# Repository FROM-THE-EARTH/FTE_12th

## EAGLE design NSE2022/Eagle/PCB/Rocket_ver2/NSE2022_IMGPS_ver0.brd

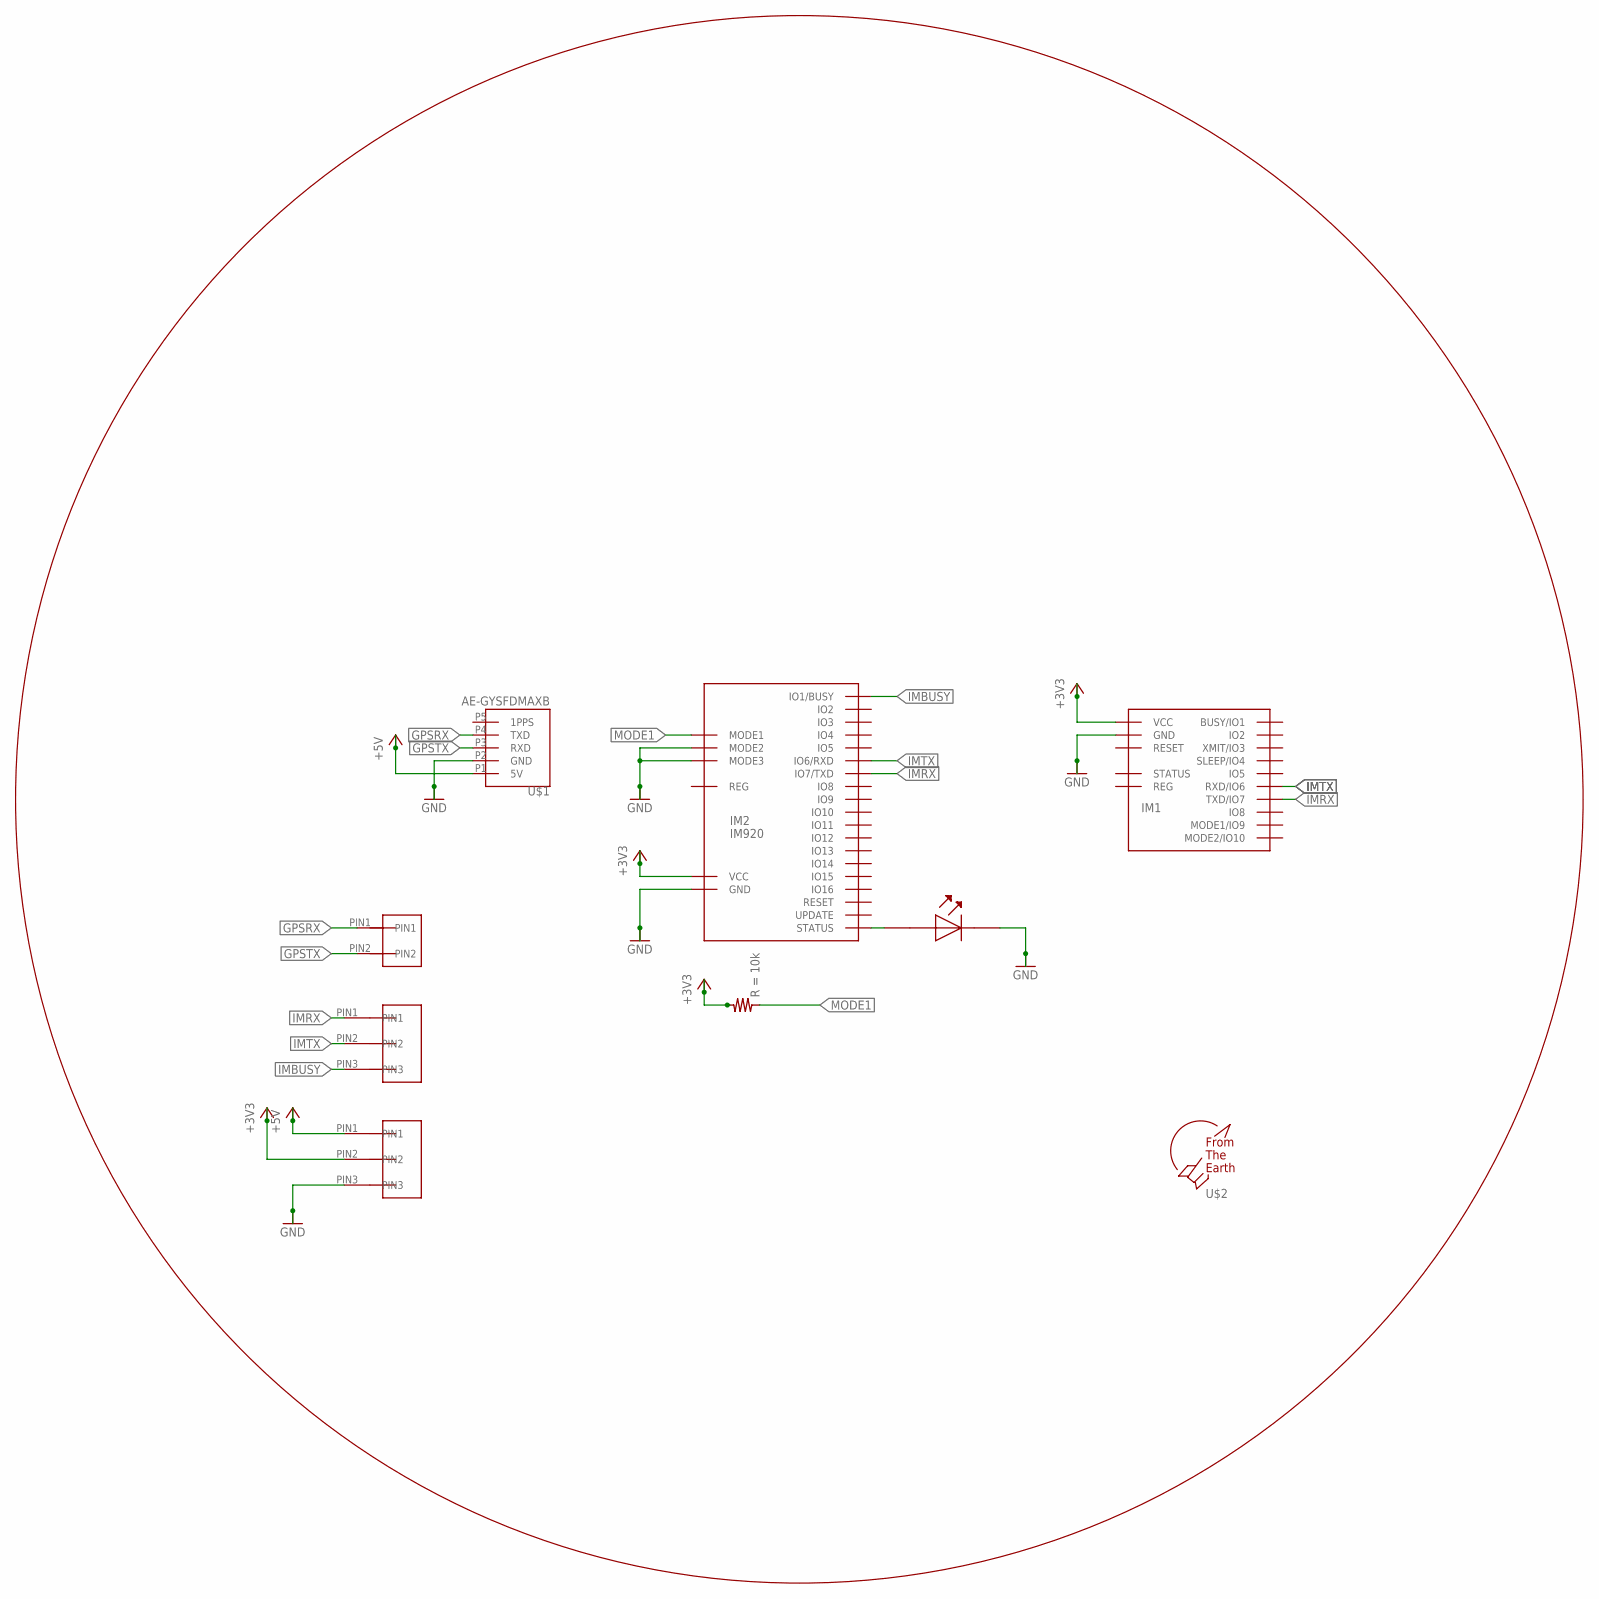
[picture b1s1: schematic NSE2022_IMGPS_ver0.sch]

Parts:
IM1: IM920C
IM2: IM920
R4: RESISTER; REGISTER
U$1: AE-GYSFDMAXB
U$2: F.T.E.LOGO; LOGO
U$33: 2PIN
U$47, U$48: 3PIN
U$54: LED

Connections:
+3V3: IM1.$P17 (VCC), IM2.IO23 (VCC), R4.B, U$48.PIN2
+5V: U$1.P1 (5V), U$48.PIN1
GND: IM1.$P18 (GND), IM2.IO18 (MODE2), IM2.IO19 (MODE3), IM2.IO24 (GND), U$1.P2 (GND), U$48.PIN3, U$54.PLUS (OUT)
GPSRX: U$1.P4 (TXD), U$33.PIN1
GPSTX: U$1.P3 (RXD), U$33.PIN2
IMBUSY: IM2.IO1 (IO1/BUSY), U$47.PIN3
IMRX: IM1.$P7 (TXD/IO7), IM2.IO7 (IO7/TXD), U$47.PIN1
IMTX: IM1.$P6 (RXD/IO6), IM2.IO6 (IO6/RXD), U$47.PIN2
MODE1: IM2.IO17 (MODE1), R4.A
unnamed: IM2.IO21 (STATUS), U$54.MINUS (IN)

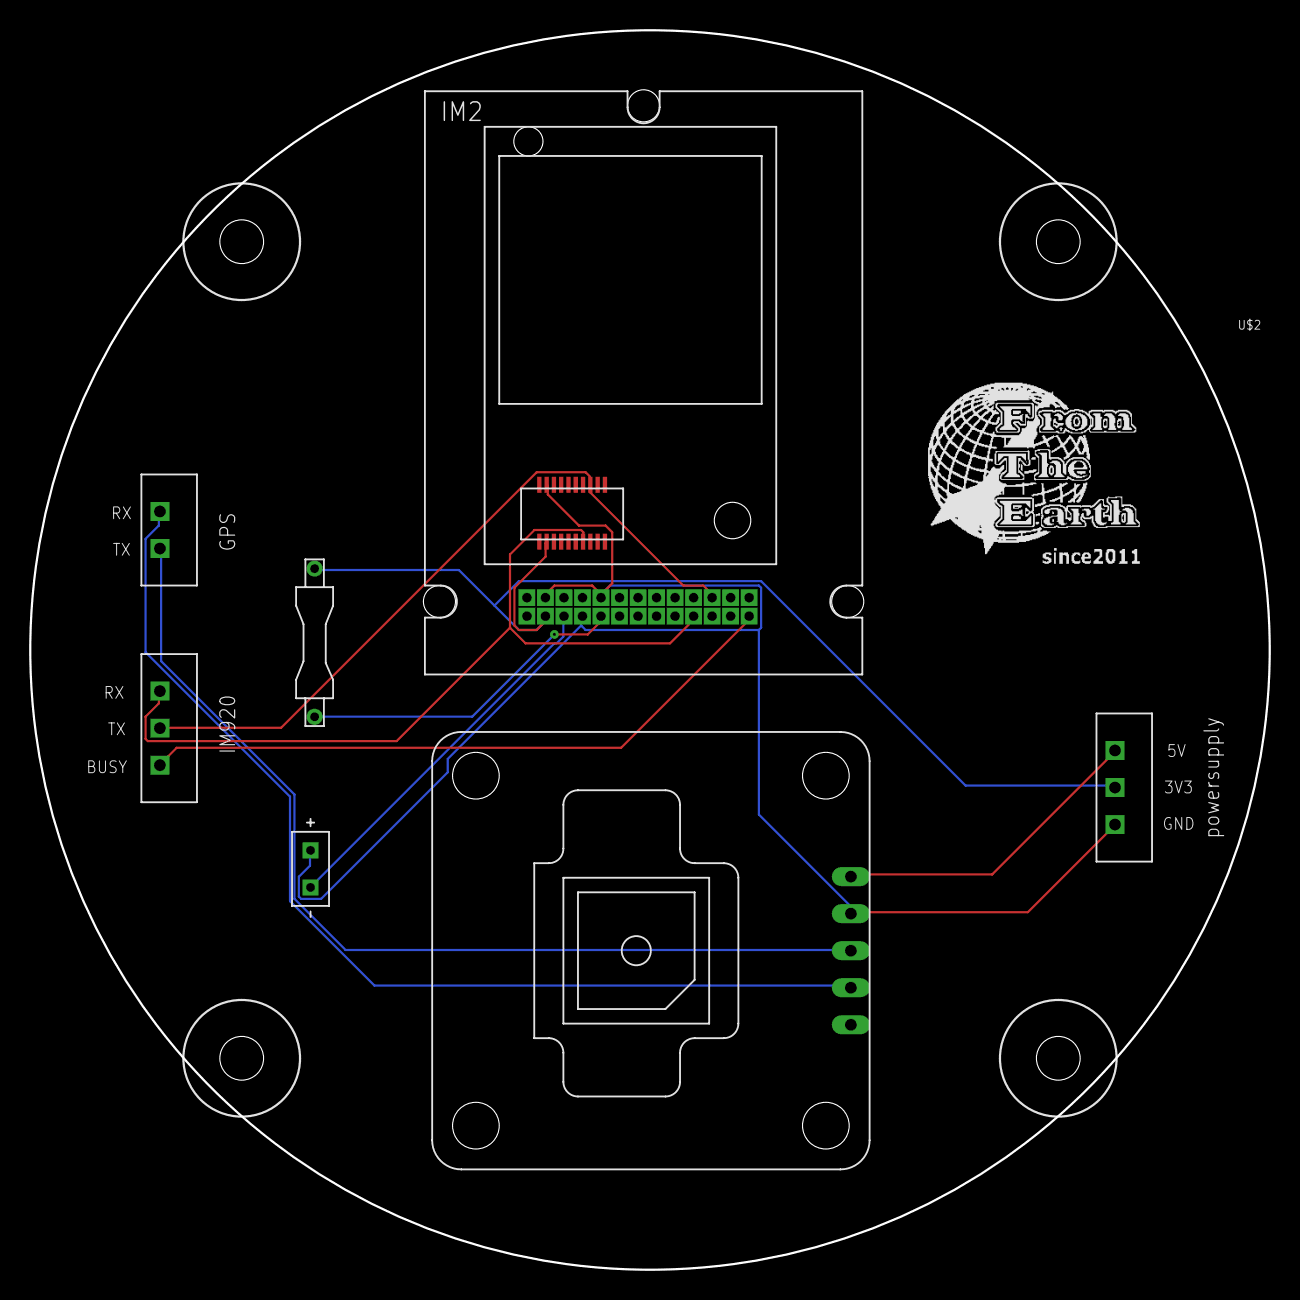
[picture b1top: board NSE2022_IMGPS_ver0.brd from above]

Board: 2 copper layers, 85.0 x 85.0 mm, 9 parts (0 on the bottom side), 10 nets.

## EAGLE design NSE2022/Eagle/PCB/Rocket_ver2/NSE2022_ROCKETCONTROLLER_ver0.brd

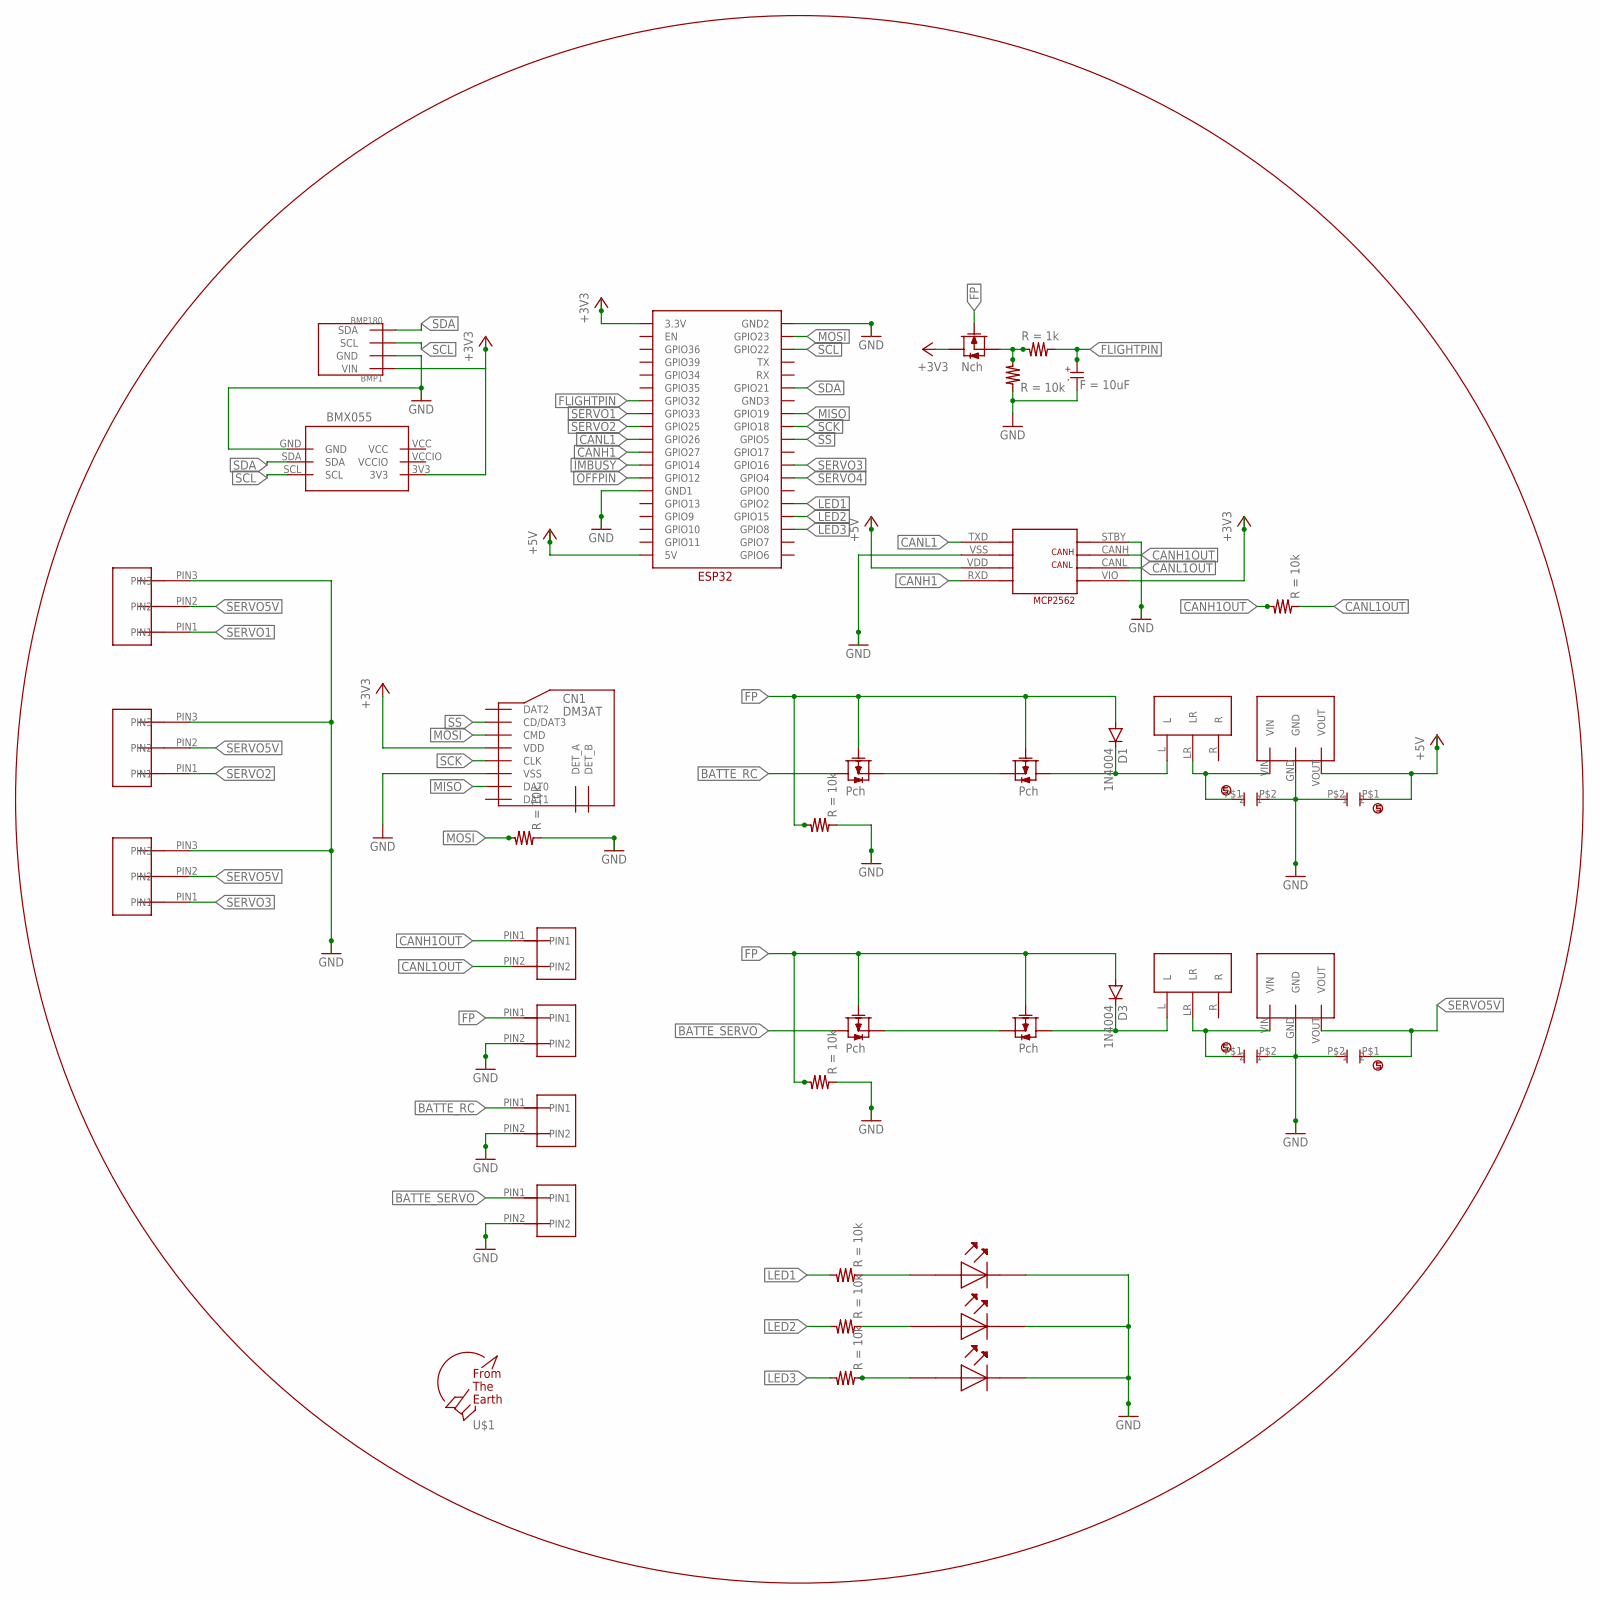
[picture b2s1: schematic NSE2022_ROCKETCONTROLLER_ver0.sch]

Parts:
BMP1: BMP180; GY-68
BMX1: BMX055
C1: CAPACITOR-ELECTROLYTIC_1
CERAMIC_CAPACITOR3, CERAMIC_CAPACITOR4, CERAMIC_CAPACITOR5, CERAMIC_CAPACITOR6: CERAMIC_CAPACITOR
CN1: DM3AT
D1, D3: 1N4004; DO41-10
R2, R3, R4, R5, R9, R10, R12, R14, R15: RESISTER; REGISTER
SRIDE_SWTCH1, SRIDE_SWTCH2: SRIDE_SWITCH
U$1: F.T.E.LOGO; LOGO
U$4: ESP32
U$8: 2SK4017-NCH; 2SK4017
U$12, U$13, U$30, U$31: 2SJ681-PCH; 2SJ681
U$14, U$32: M78AR05-1
U$18, U$19, U$20, U$21: 2PIN
U$27: MCP2562
U$42, U$43, U$44: 3PIN
U$63, U$64, U$69: LED

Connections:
+3V3: BMP1.P1 (VIN), BMX1.3V3, CN1.VDD, U$4.3.3V, U$8.DRAIN, U$27.VIO
+5V: CERAMIC_CAPACITOR5.P$1 (1), U$4.5V, U$27.VDD, U$32.VOUT
BATTE_RC: U$20.PIN1, U$30.DRAIN
BATTE_SERVO: U$13.DRAIN, U$21.PIN1
CANH1: U$4.GPIO27, U$27.RXD
CANH1OUT: R3.B, U$18.PIN1, U$27.CANH
CANL1: U$4.GPIO26, U$27.TXD
CANL1OUT: R3.A, U$18.PIN2, U$27.CANL
FLIGHTPIN: C1.KS, R10.A, U$4.GPIO32
FP: D1.A, D3.A, R2.B, R5.B, U$8.GATE, U$12.GATE, U$13.GATE, U$19.PIN1, U$30.GATE, U$31.GATE
GND: BMP1.P2 (GND), BMX1.GND, C1.AN, CERAMIC_CAPACITOR3.P$2 (2), CERAMIC_CAPACITOR4.P$2 (2), CERAMIC_CAPACITOR5.P$2 (2), CERAMIC_CAPACITOR6.P$2 (2), CN1.VSS, R2.A, R4.A, R5.A, R9.A, U$4.GND1, U$14.GND, U$19.PIN2, U$20.PIN2, U$21.PIN2, U$27.STBY, U$27.VSS, U$32.GND, U$42.PIN3, U$43.PIN3, U$44.PIN3, U$63.PLUS (OUT), U$64.PLUS (OUT), U$69.PLUS (OUT)
IMBUSY: U$4.GPIO14
LED1: R12.B, U$4.GPIO2
LED2: R14.B, U$4.GPIO15
LED3: R15.B, U$4.GPIO8
MISO: CN1.DAT0, U$4.GPIO19
MOSI: CN1.CMD, R4.B, U$4.GPIO23
unnamed: U$12.SOURCE, U$13.SOURCE
unnamed: R9.B, R10.B, U$8.SOURCE
unnamed 20: CERAMIC_CAPACITOR4.P$1 (1), SRIDE_SWTCH1.LR, U$14.VIN; also elsewhere on the board
unnamed 21: D1.C, SRIDE_SWTCH2.L, U$31.DRAIN; also elsewhere on the board
unnamed 22: D3.C, SRIDE_SWTCH1.L, U$12.DRAIN; also elsewhere on the board
unnamed: R12.A, U$63.MINUS (IN)
unnamed: R14.A, U$64.MINUS (IN)
unnamed: R15.A, U$69.MINUS (IN)
unnamed: U$30.SOURCE, U$31.SOURCE
unnamed 27: CERAMIC_CAPACITOR6.P$1 (1), SRIDE_SWTCH2.LR, U$32.VIN; also elsewhere on the board
OFFPIN: U$4.GPIO12
SCK: CN1.CLK, U$4.GPIO18
SCL: BMP1.P3 (SCL), BMX1.SCL, U$4.GPIO22
SDA: BMP1.P4 (SDA), BMX1.SDA, U$4.GPIO21
SERVO1: U$4.GPIO33, U$42.PIN1
SERVO2: U$4.GPIO25, U$43.PIN1
SERVO3: U$4.GPIO16, U$44.PIN1
SERVO4: U$4.GPIO4
SERVO5V: CERAMIC_CAPACITOR3.P$1 (1), U$14.VOUT, U$42.PIN2, U$43.PIN2, U$44.PIN2
SS: CN1.CD/DAT3, U$4.GPIO5
VCC: BMX1.VCC
VCCIO: BMX1.VCCIO

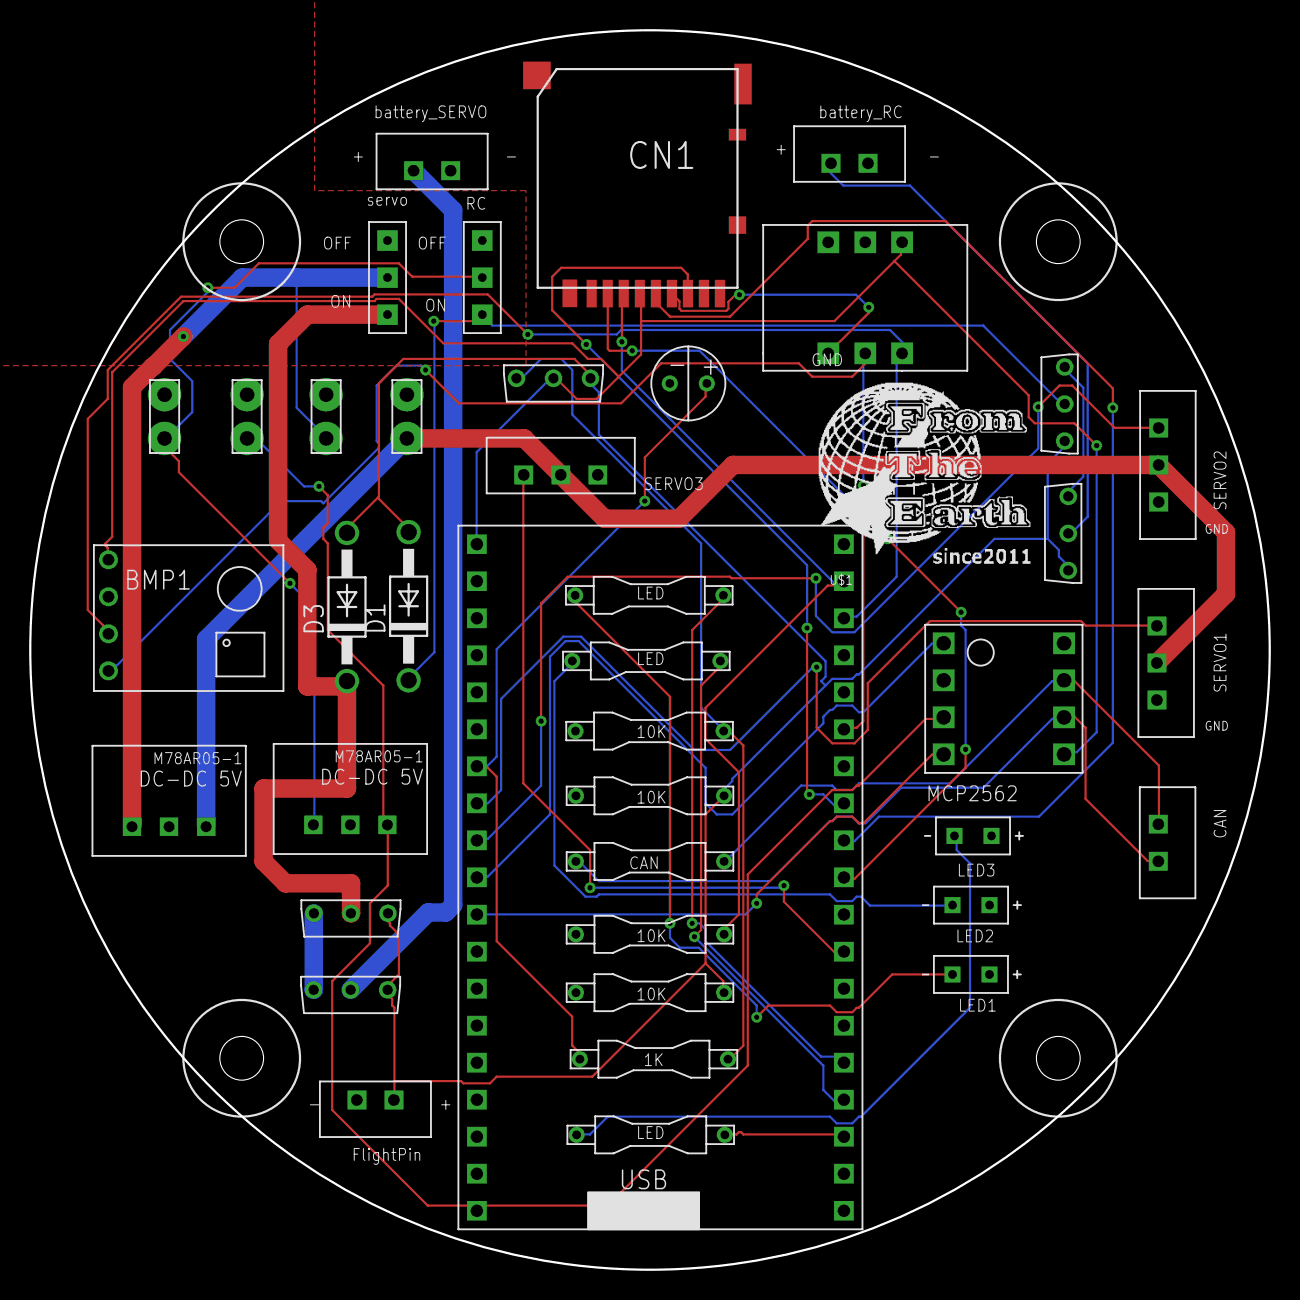
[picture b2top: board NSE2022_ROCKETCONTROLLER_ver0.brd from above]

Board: 2 copper layers, 85.0 x 85.0 mm, 41 parts (0 on the bottom side), 34 nets.

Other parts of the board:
U$2, U$3: SLIDESWITCH

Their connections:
unnamed 20: U$3.C; also elsewhere on the board
unnamed 21: U$2.A; also elsewhere on the board
unnamed 22: U$3.A; also elsewhere on the board
unnamed 27: U$2.C; also elsewhere on the board

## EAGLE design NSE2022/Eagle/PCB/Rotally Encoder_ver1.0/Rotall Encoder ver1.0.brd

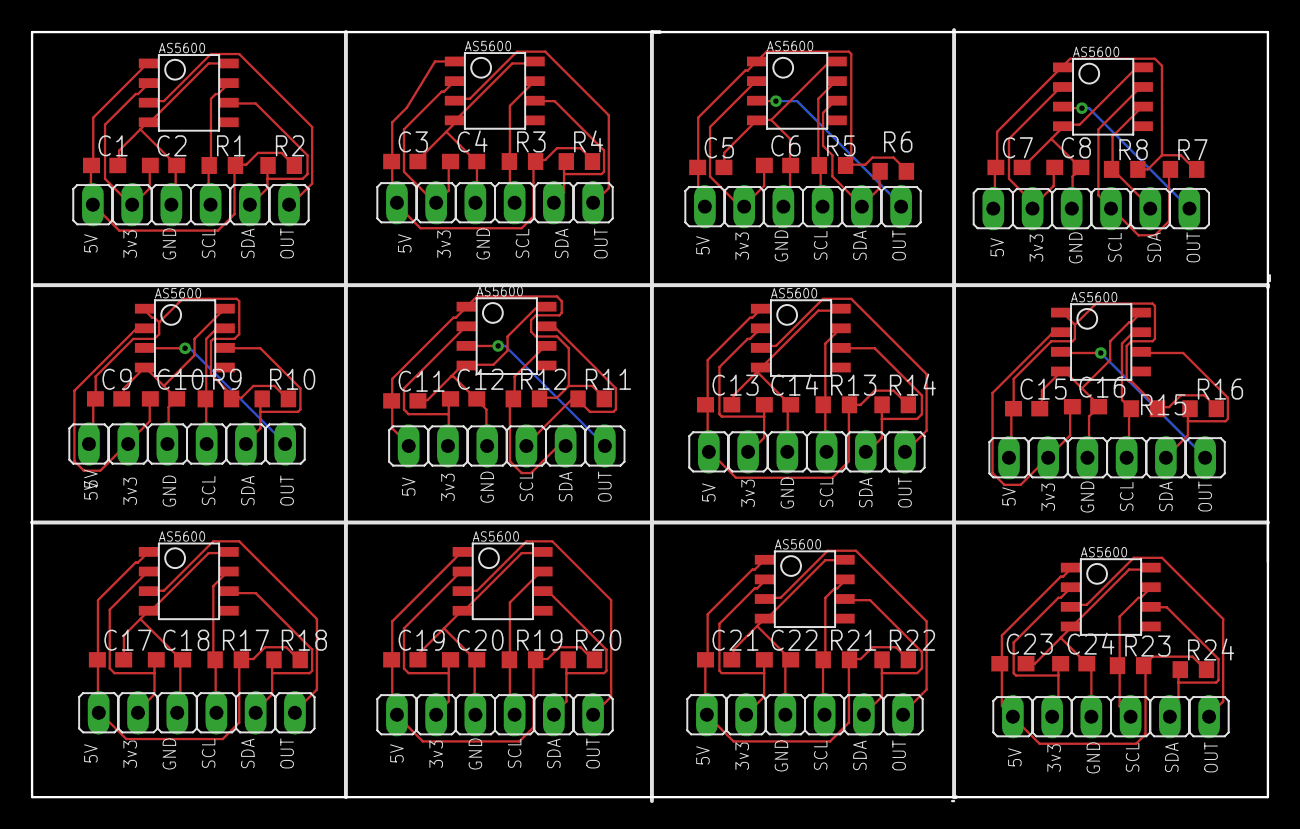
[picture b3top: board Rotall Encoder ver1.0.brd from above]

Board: 2 copper layers, 80.0 x 49.5 mm, 72 parts (0 on the bottom side), 6 nets.

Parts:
C1, C2, C3, C4, C5, C6, C7, C8, C9, C10, C11, C12, C13, C14, C15, C16, C17, C18, C19, C20, C21, C22, C23, C24: C0603
JP1, JP2, JP3, JP4, JP5, JP6, JP7, JP8, JP9, JP10, JP11, JP12: 06X01
R1, R2, R3, R4, R5, R6, R7, R8, R9, R10, R11, R12, R13, R14, R15, R16, R17, R18, R19, R20, R21, R22, R23, R24: R0603
U1, U2, U3, U4, U5, U6, U7, U8, U9, U10, U11, U12: AS5600

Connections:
+3V3: C2.1, C4.1, C6.1, C8.1, C10.1, C12.1, C14.1, C16.1, C18.1, C20.1, C22.1, C24.1, JP1.2, JP2.2, JP3.2, JP4.2, JP5.2, JP6.2, JP7.2, JP8.2, JP9.2, JP10.2, JP11.2, JP12.2, U1.VDD3V3, U2.VDD3V3, U3.VDD3V3, U4.VDD3V3, U5.VDD3V3, U6.VDD3V3, U7.VDD3V3, U8.VDD3V3, U9.VDD3V3, U10.VDD3V3, U11.VDD3V3, U12.VDD3V3
+5V: C1.1, C3.1, C5.1, C7.1, C9.1, C11.1, C13.1, C15.1, C17.1, C19.1, C21.1, C23.1, JP1.1, JP2.1, JP3.1, JP4.1, JP5.1, JP6.1, JP7.1, JP8.1, JP9.1, JP10.1, JP11.1, JP12.1, R1.2, R2.2, R3.2, R4.2, R5.2, R6.2, R7.2, R8.2, R9.2, R10.2, R11.2, R12.2, R13.2, R14.2, R15.2, R16.2, R17.2, R18.2, R19.2, R20.2, R21.2, R22.2, R23.2, R24.2, U1.VDD5V, U2.VDD5V, U3.VDD5V, U4.VDD5V, U5.VDD5V, U6.VDD5V, U7.VDD5V, U8.VDD5V, U9.VDD5V, U10.VDD5V, U11.VDD5V, U12.VDD5V
GND: C1.2, C2.2, C3.2, C4.2, C5.2, C6.2, C7.2, C8.2, C9.2, C10.2, C11.2, C12.2, C13.2, C14.2, C15.2, C16.2, C17.2, C18.2, C19.2, C20.2, C21.2, C22.2, C23.2, C24.2, JP1.3, JP2.3, JP3.3, JP4.3, JP5.3, JP6.3, JP7.3, JP8.3, JP9.3, JP10.3, JP11.3, JP12.3, U1.DIR, U1.GND, U2.DIR, U2.GND, U3.DIR, U3.GND, U4.DIR, U4.GND, U5.DIR, U5.GND, U6.DIR, U6.GND, U7.DIR, U7.GND, U8.DIR, U8.GND, U9.DIR, U9.GND, U10.DIR, U10.GND, U11.DIR, U11.GND, U12.DIR, U12.GND
OUT: JP1.6, JP2.6, JP3.6, JP4.6, JP5.6, JP6.6, JP7.6, JP8.6, JP9.6, JP10.6, JP11.6, JP12.6, U1.OUT, U2.OUT, U3.OUT, U4.OUT, U5.OUT, U6.OUT, U7.OUT, U8.OUT, U9.OUT, U10.OUT, U11.OUT, U12.OUT
SCL: JP1.4, JP2.4, JP3.4, JP4.4, JP5.4, JP6.4, JP7.4, JP8.4, JP9.4, JP10.4, JP11.4, JP12.4, R1.1, R3.1, R5.1, R7.1, R9.1, R11.1, R13.1, R15.1, R17.1, R19.1, R21.1, R23.1, U1.SCL, U2.SCL, U3.SCL, U4.SCL, U5.SCL, U6.SCL, U7.SCL, U8.SCL, U9.SCL, U10.SCL, U11.SCL, U12.SCL
SDA: JP1.5, JP2.5, JP3.5, JP4.5, JP5.5, JP6.5, JP7.5, JP8.5, JP9.5, JP10.5, JP11.5, JP12.5, R2.1, R4.1, R6.1, R8.1, R10.1, R12.1, R14.1, R16.1, R18.1, R20.1, R22.1, R24.1, U1.SDA, U2.SDA, U3.SDA, U4.SDA, U5.SDA, U6.SDA, U7.SDA, U8.SDA, U9.SDA, U10.SDA, U11.SDA, U12.SDA

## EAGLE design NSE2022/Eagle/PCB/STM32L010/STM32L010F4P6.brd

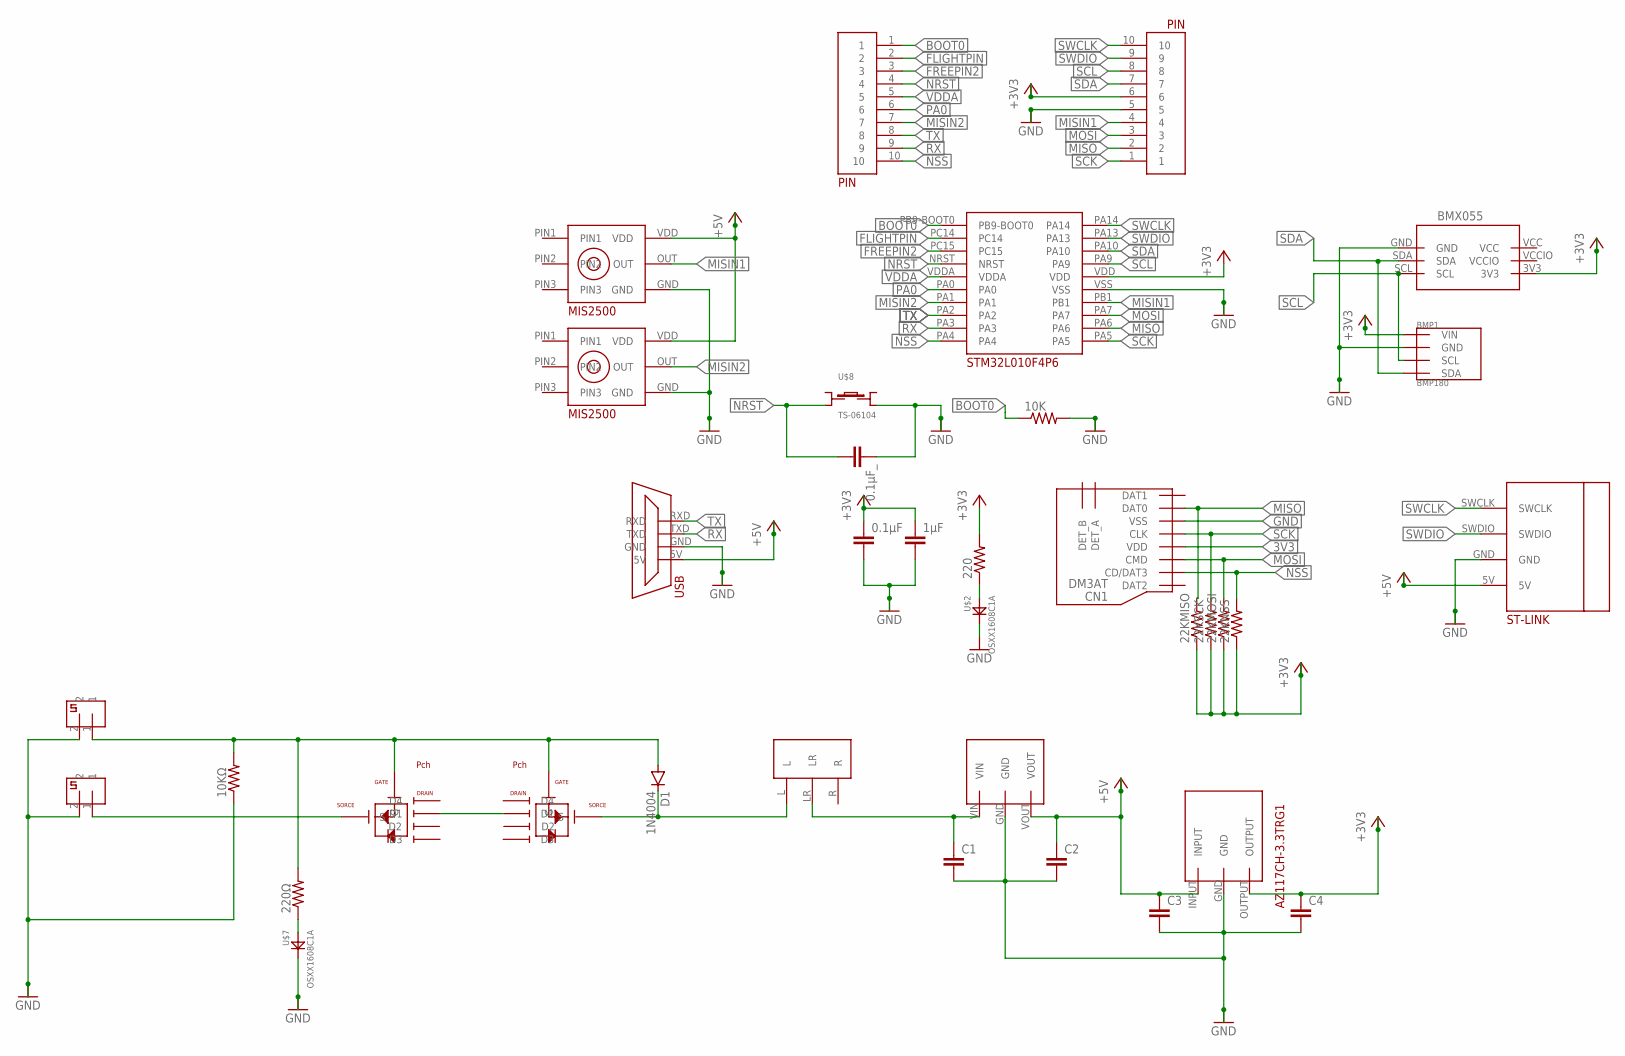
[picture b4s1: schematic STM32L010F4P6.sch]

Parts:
0.1μF, 0.1μF_: C-EUC0603; C0603
1μF: C-EUC0805; C0805
10K, 10KΩ, 22KMISO, 22KMOSI, 22KNSS, 22KSCK, 220, 220Ω: R-US_R0603; R0603
BMP1: BMP180; GY-68
BMX1: BMX055
C1, C2, C3, C4: C2,5-3; C2.5-3
CN1: DM3AT
CONNECTOR1, CONNECTOR3: 2PIN
D1: 1N4004; DO41-10
SRIDE_SWTCH1: SRIDE_SWITCH
U$1: STM32L010F4P6
U$2, U$7: OSXX1608C1A
U$3, U$4: MIS2500
U$5: STLINK
U$6, U$9: SSM6J808R
U$8: TS-06104
U$11: M78AR05-1
U$12, U$13: 10PIN
U$14: F234X; FT234X
U$17: AZ117CH-3.3TRG1

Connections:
3V3: CN1.VDD
+3V3: 0.1μF.1, 1μF.1, 22KMISO.1, 22KMOSI.1, 22KNSS.1, 22KSCK.1, 220.2, BMP1.P1 (VIN), BMX1.3V3, C4.1, U$1.VDD, U$13.6, U$17.OUTPUT
+5V: C2.1, C3.1, U$3.VDD, U$4.VDD, U$5.5V, U$11.VOUT, U$14.5V, U$17.INPUT
BOOT0: 10K.1, U$1.PB9-BOOT0, U$12.1
EXIN: 10KΩ.2, 220Ω.2, CONNECTOR1.1, D1.A, U$6.G, U$9.G
FLIGHTPIN: U$1.PC14, U$12.2
FREEPIN2: U$1.PC15, U$12.3
GND: 0.1μF.2, 0.1μF_.1, 1μF.2, 10K.2, 10KΩ.1, BMP1.P2 (GND), BMX1.GND, C1.2, C2.2, C3.2, C4.2, CN1.VSS, CONNECTOR1.2, CONNECTOR3.2, U$1.VSS, U$2.CT, U$3.GND, U$4.GND, U$5.GND, U$7.CT, U$8.D, U$11.GND, U$13.5, U$14.GND, U$17.GND
MISIN1: U$1.PB1, U$3.OUT, U$13.4
MISIN2: U$1.PA1, U$4.OUT, U$12.7
MISO: 22KMISO.2, CN1.DAT0, U$1.PA6, U$13.2
MOSI: 22KMOSI.2, CN1.CMD, U$1.PA7, U$13.3
unnamed: U$6.D1, U$9.D1
unnamed: D1.C, SRIDE_SWTCH1.L, U$9.S
unnamed: CONNECTOR3.1, U$6.S
unnamed: C1.1, SRIDE_SWTCH1.LR, U$11.VIN
unnamed: 220.1, U$2.AN
unnamed: 220Ω.1, U$7.AN
NRST: 0.1μF_.2, U$1.NRST, U$8.B, U$12.4
NSS: 22KNSS.2, CN1.CD/DAT3, U$1.PA4, U$12.10
PA0: U$1.PA0, U$12.6
RX: U$1.PA3, U$12.9, U$14.TXD
SCK: 22KSCK.2, CN1.CLK, U$1.PA5, U$13.1
SCL: BMP1.P3 (SCL), BMX1.SCL, U$1.PA9, U$13.8
SDA: BMX1.SDA, U$1.PA10, U$13.7
SWCLK: U$1.PA14, U$5.SWCLK, U$13.10
SWDIO: U$1.PA13, U$5.SWDIO, U$13.9
TX: U$1.PA2, U$12.8, U$14.RXD
VCC: BMX1.VCC
VCCIO: BMX1.VCCIO
VDDA: U$1.VDDA, U$12.5

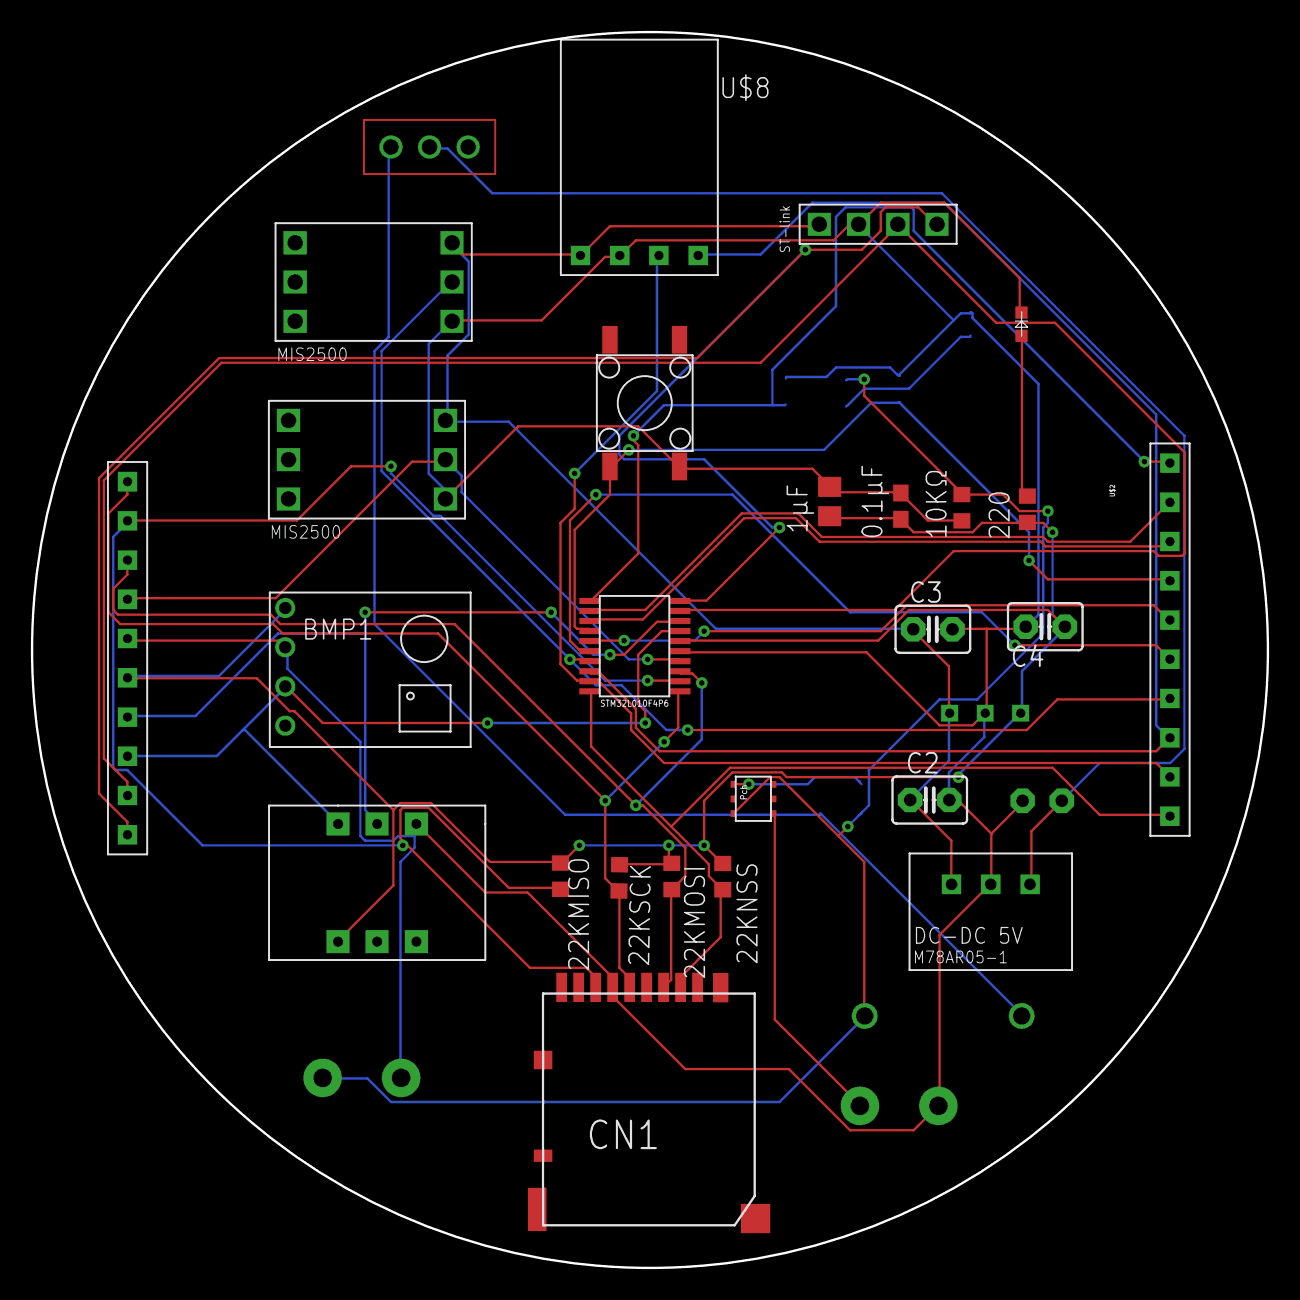
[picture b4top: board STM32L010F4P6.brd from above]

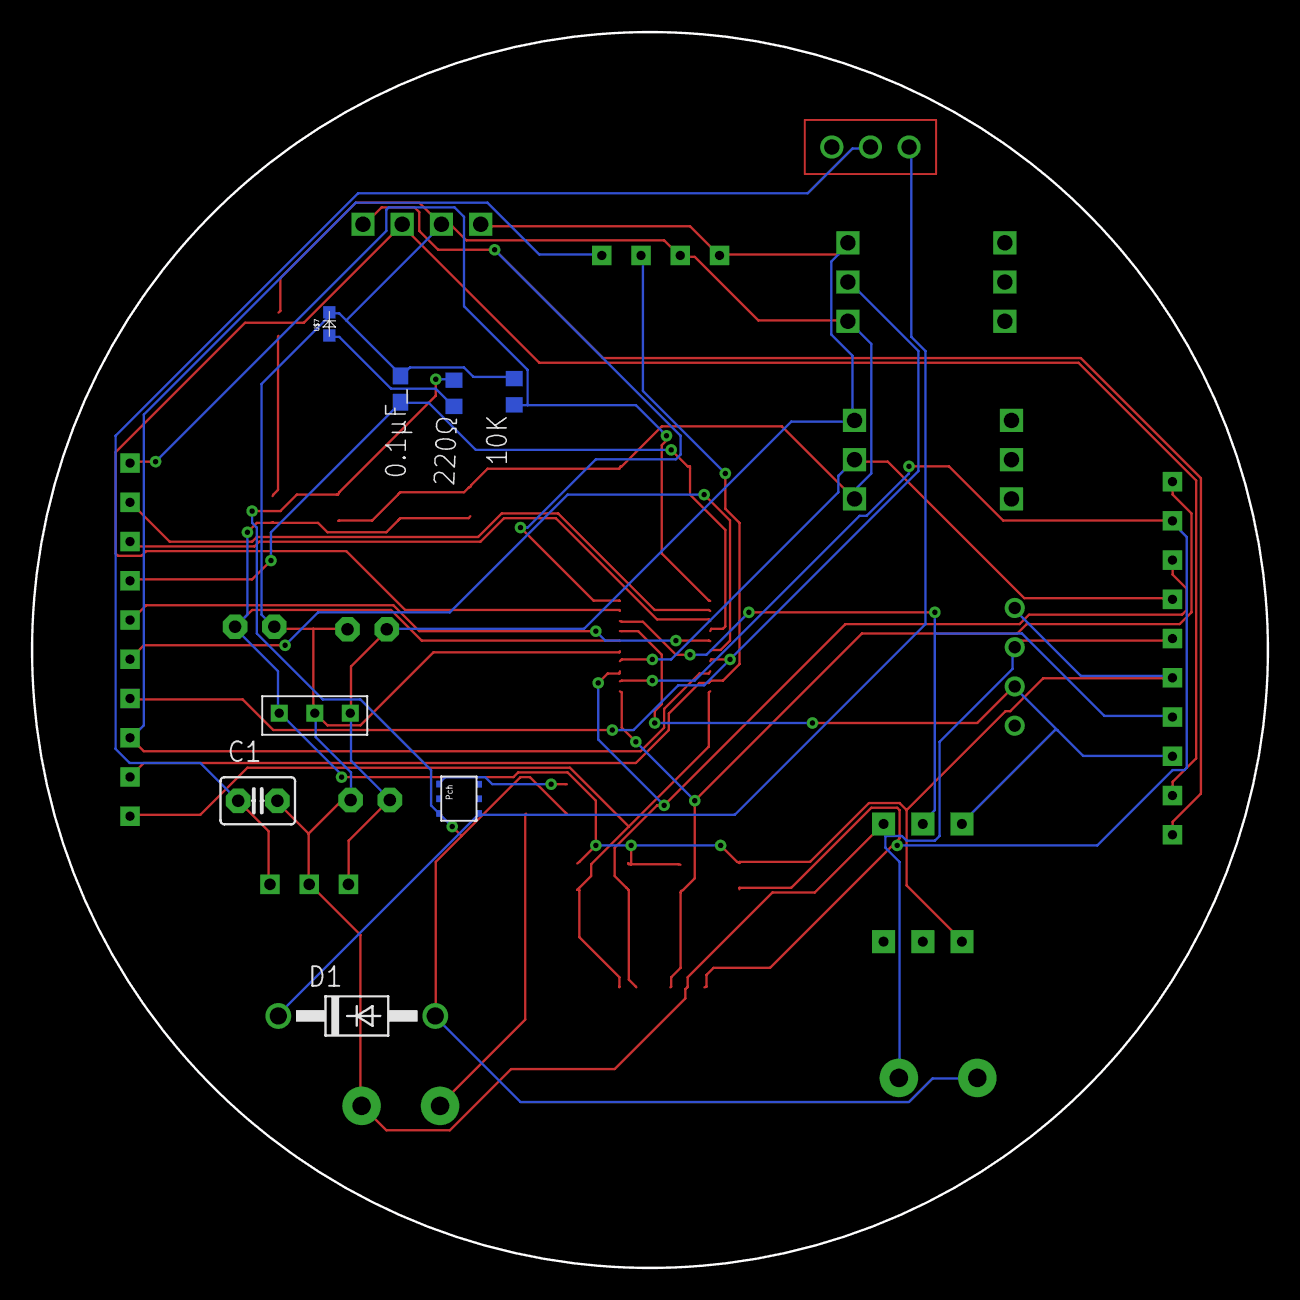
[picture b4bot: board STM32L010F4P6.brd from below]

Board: 2 copper layers, 80.0 x 80.0 mm, 36 parts (8 on the bottom side), 28 nets.
